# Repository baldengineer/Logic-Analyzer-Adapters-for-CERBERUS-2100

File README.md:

# CERBERUS 2100 Logic Analyzer Adapters

These adapters allow you to connect a logic analyzer to the CERBERUS 2100 expansion port--while having an expansion board connected.

For more information on the computer, check out the [CERBERUS 2100 project page](https://www.thebyteattic.com/p/cerberus-2100.html).

## One-To-One Adapter 
This adapter replicates the CERBERUS 2100's expansion port three times. Pins are mapped "1 to 1" across all three.

## Digital Digital Discovery Adapter
This adapter connects directly to a Digilent Digital Discovery and an expansion board. The signals on the left are grouped to match the input of the Digital Discovery.

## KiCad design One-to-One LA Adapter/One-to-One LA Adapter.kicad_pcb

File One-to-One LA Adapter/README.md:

## One-To-One Adapter

The One-to-one has three connectors. The middle connector plugs into the CERBERUS 2100's socket. The left header is intended for a logic analyzer. The right header is intended for an expansion board.

However, all three headers are connected in parallel.

### Status
Rev1 sent to fab. Still need to make Waveforms template and test the boards.

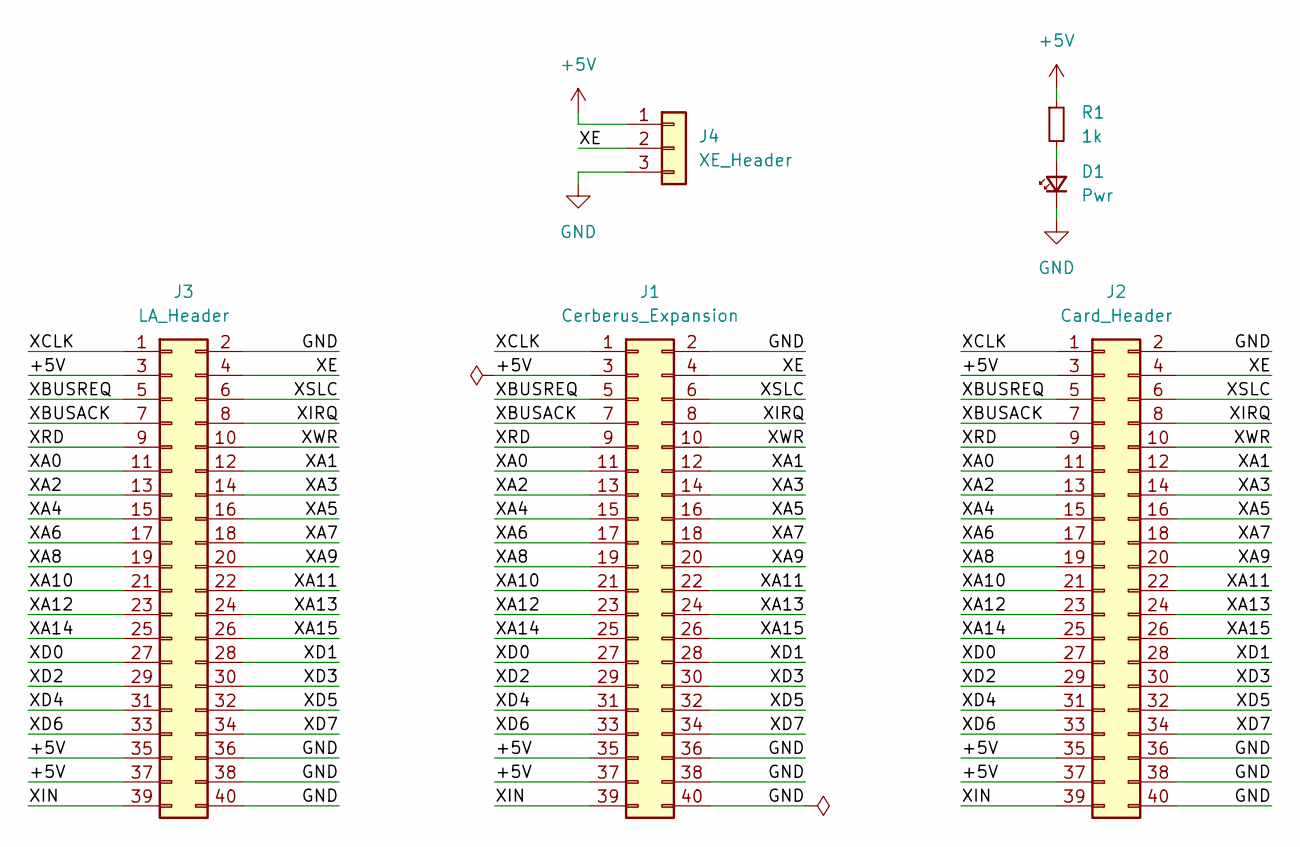
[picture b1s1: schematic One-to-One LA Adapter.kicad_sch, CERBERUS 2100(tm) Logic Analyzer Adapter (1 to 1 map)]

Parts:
D1: Pwr; LED_1206_3216Metric_Pad1.42x1.75mm_HandSolder
J1: Cerberus_Expansion; PinSocket_2x20_P2.54mm_Vertical
J2: Card_Header; PinHeader_2x20_P2.54mm_Vertical
J3: LA_Header; PinHeader_2x20_P2.54mm_Vertical
J4: XE_Header; PinHeader_1x03_P2.54mm_Vertical
R1: 1k; R_0805_2012Metric_Pad1.20x1.40mm_HandSolder

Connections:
+5V: J1.3, J1.35, J1.37, J2.3, J2.35, J2.37, J3.3, J3.35, J3.37, J4.1, R1.1
/XA0: J1.11, J2.11, J3.11
/XA1: J1.12, J2.12, J3.12
/XA2: J1.13, J2.13, J3.13
/XA3: J1.14, J2.14, J3.14
/XA4: J1.15, J2.15, J3.15
/XA5: J1.16, J2.16, J3.16
/XA6: J1.17, J2.17, J3.17
/XA7: J1.18, J2.18, J3.18
/XA8: J1.19, J2.19, J3.19
/XA9: J1.20, J2.20, J3.20
/XA10: J1.21, J2.21, J3.21
/XA11: J1.22, J2.22, J3.22
/XA12: J1.23, J2.23, J3.23
/XA13: J1.24, J2.24, J3.24
/XA14: J1.25, J2.25, J3.25
/XA15: J1.26, J2.26, J3.26
/XBUSACK: J1.7, J2.7, J3.7
/XBUSREQ: J1.5, J2.5, J3.5
/XCLK: J1.1, J2.1, J3.1
/XD0: J1.27, J2.27, J3.27
/XD1: J1.28, J2.28, J3.28
/XD2: J1.29, J2.29, J3.29
/XD3: J1.30, J2.30, J3.30
/XD4: J1.31, J2.31, J3.31
/XD5: J1.32, J2.32, J3.32
/XD6: J1.33, J2.33, J3.33
/XD7: J1.34, J2.34, J3.34
/XE: J1.4, J2.4, J3.4, J4.2
/XIN: J1.39, J2.39, J3.39
/XIRQ: J1.8, J2.8, J3.8
/XRD: J1.9, J2.9, J3.9
/XSLC: J1.6, J2.6, J3.6
/XWR: J1.10, J2.10, J3.10
GND: D1.1 (K), J1.2, J1.36, J1.38, J1.40, J2.2, J2.36, J2.38, J2.40, J3.2, J3.36, J3.38, J3.40, J4.3
unnamed: D1.2 (A), R1.2

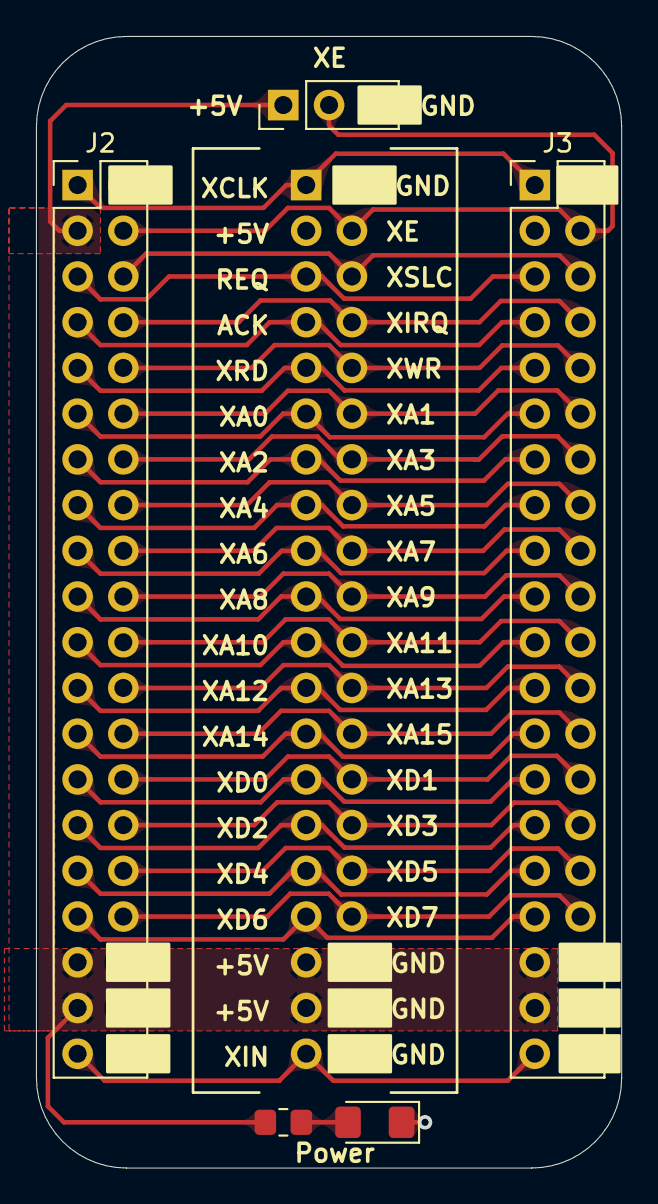
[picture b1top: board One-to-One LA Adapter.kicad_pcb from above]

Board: 2 copper layers, 32.5 x 62.9 mm, 6 parts (1 on the bottom side), 36 nets.

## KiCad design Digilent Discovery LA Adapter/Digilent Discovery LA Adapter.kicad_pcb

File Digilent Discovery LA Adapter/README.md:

## Digilent Discovery LA Adapter

This adapter is inteded to be used with a [Digilent Digital Discovery](https://digilent.com/shop/digital-discovery-portable-usb-logic-analyzer-and-digital-pattern-generator/). (Not the Analog Discovery!) These are USB-based logic analyzers that sample up to 100 MHz and 32 signals.

The center connector plugs into the socket. The right connector is for an expansion card. The left connector is for the Digital Discovery. 

Three connection options:
1. Use a short ribbon cable.
2. Mount the header upside-down.
3. Mount the header top-side-up.

### Waveforms Project File
Use the latest [beta version of Waveforms](https://forum.digilent.com/topic/8908-waveforms-beta-download/).

There is a bug with the pattern trigger. Addresses are reversed. So, to trigger on `0x0205` (`0000 0010 0000 0101`) you need to set the pattern to `0xA040` (`1010 0000 0100 0000`).

The clocks and control signals connect to the 24-32 inputs.

**CERBERUS 2100 Digital Discovery Template.dwf3work** is a starting project. It has all of the signals mapped for you! 

### Build Notes
Easily connect a Digilent Digital Discovery to a CERBERUS 2100. At a minimum, you'll need a 40-pin socket and a right-angle 32-pin socket. To act as an interposer between the CERBERUS and expansion card, you need a 40-pin header. There's also a spot for a 0805 resistor and 1206 LED for bling.

### OSH Park Link
The KiCad design files and PCB gerbers are available. Or you can order these boards directly from [OSH Park using this link](https://oshpark.com/shared_projects/0LsKYepP).

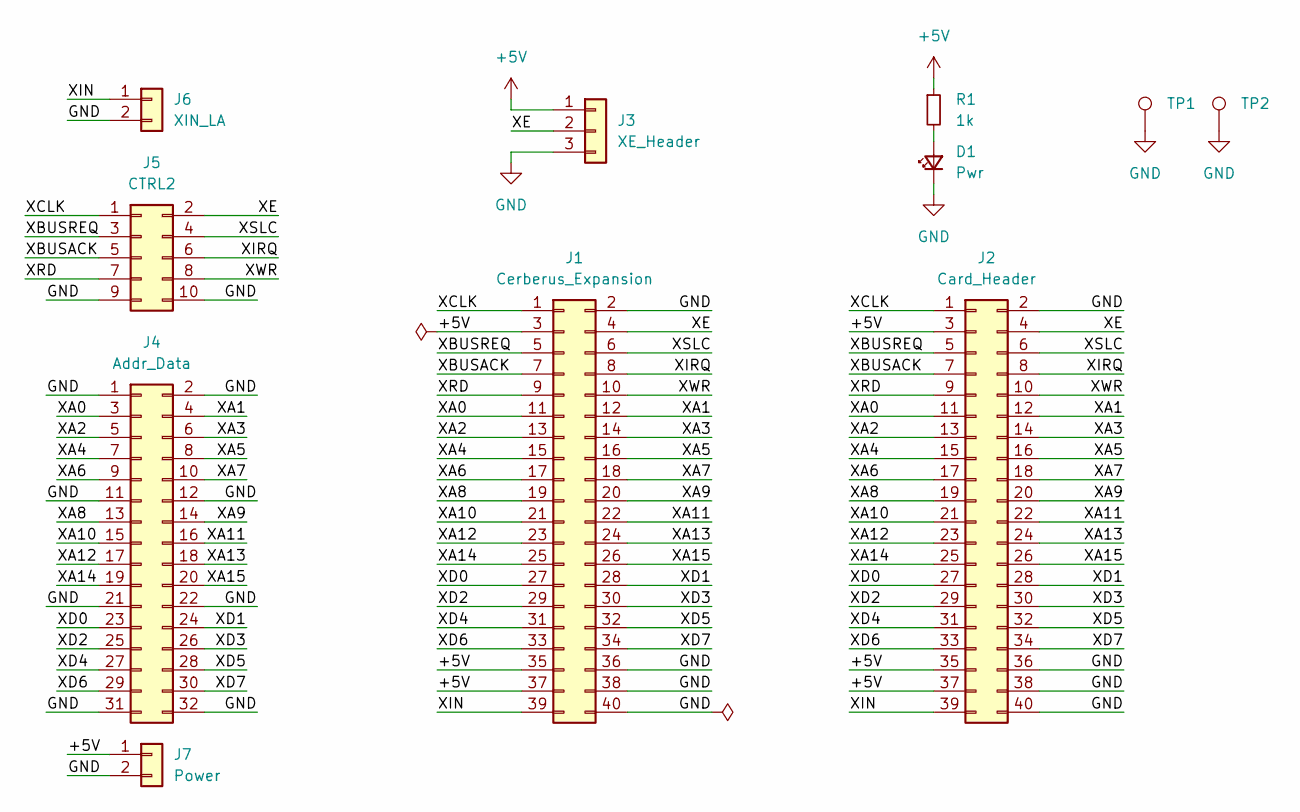
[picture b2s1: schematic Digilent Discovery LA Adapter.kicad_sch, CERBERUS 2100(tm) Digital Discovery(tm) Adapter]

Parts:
D1: Pwr; LED_1206_3216Metric_Pad1.42x1.75mm_HandSolder
J1: Cerberus_Expansion; PinSocket_2x20_P2.54mm_Vertical
J2: Card_Header; PinHeader_2x20_P2.54mm_Vertical
J3: XE_Header; PinHeader_1x03_P2.54mm_Vertical
J4: Addr_Data; PinSocket_2x16_P2.54mm_Vertical
J5: CTRL2; PinSocket_2x05_P2.54mm_Vertical
J6: XIN_LA; PinHeader_1x02_P2.54mm_Vertical
J7: Power; PinHeader_1x02_P2.54mm_Vertical
R1: 1k; R_0805_2012Metric_Pad1.20x1.40mm_HandSolder
TP1, TP2: TestPoint_Harwin; Harwin-S1751-46-Test-Point

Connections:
+5V: J1.3, J1.35, J1.37, J2.3, J2.35, J2.37, J3.1, J7.1, R1.1
/XA0: J1.11, J2.11, J4.3
/XA1: J1.12, J2.12, J4.4
/XA2: J1.13, J2.13, J4.5
/XA3: J1.14, J2.14, J4.6
/XA4: J1.15, J2.15, J4.7
/XA5: J1.16, J2.16, J4.8
/XA6: J1.17, J2.17, J4.9
/XA7: J1.18, J2.18, J4.10
/XA8: J1.19, J2.19, J4.13
/XA9: J1.20, J2.20, J4.14
/XA10: J1.21, J2.21, J4.15
/XA11: J1.22, J2.22, J4.16
/XA12: J1.23, J2.23, J4.17
/XA13: J1.24, J2.24, J4.18
/XA14: J1.25, J2.25, J4.19
/XA15: J1.26, J2.26, J4.20
/XBUSACK: J1.7, J2.7, J5.5
/XBUSREQ: J1.5, J2.5, J5.3
/XCLK: J1.1, J2.1, J5.1
/XD0: J1.27, J2.27, J4.23
/XD1: J1.28, J2.28, J4.24
/XD2: J1.29, J2.29, J4.25
/XD3: J1.30, J2.30, J4.26
/XD4: J1.31, J2.31, J4.27
/XD5: J1.32, J2.32, J4.28
/XD6: J1.33, J2.33, J4.29
/XD7: J1.34, J2.34, J4.30
/XE: J1.4, J2.4, J3.2, J5.2
/XIN: J1.39, J2.39, J6.1
/XIRQ: J1.8, J2.8, J5.6
/XRD: J1.9, J2.9, J5.7
/XSLC: J1.6, J2.6, J5.4
/XWR: J1.10, J2.10, J5.8
GND: D1.1 (K), J1.2, J1.36, J1.38, J1.40, J2.2, J2.36, J2.38, J2.40, J3.3, J4.1, J4.2, J4.11, J4.12, J4.21, J4.22, J4.31, J4.32, J5.9, J5.10, J6.2, J7.2, TP1.1, TP2.1
unnamed: D1.2 (A), R1.2

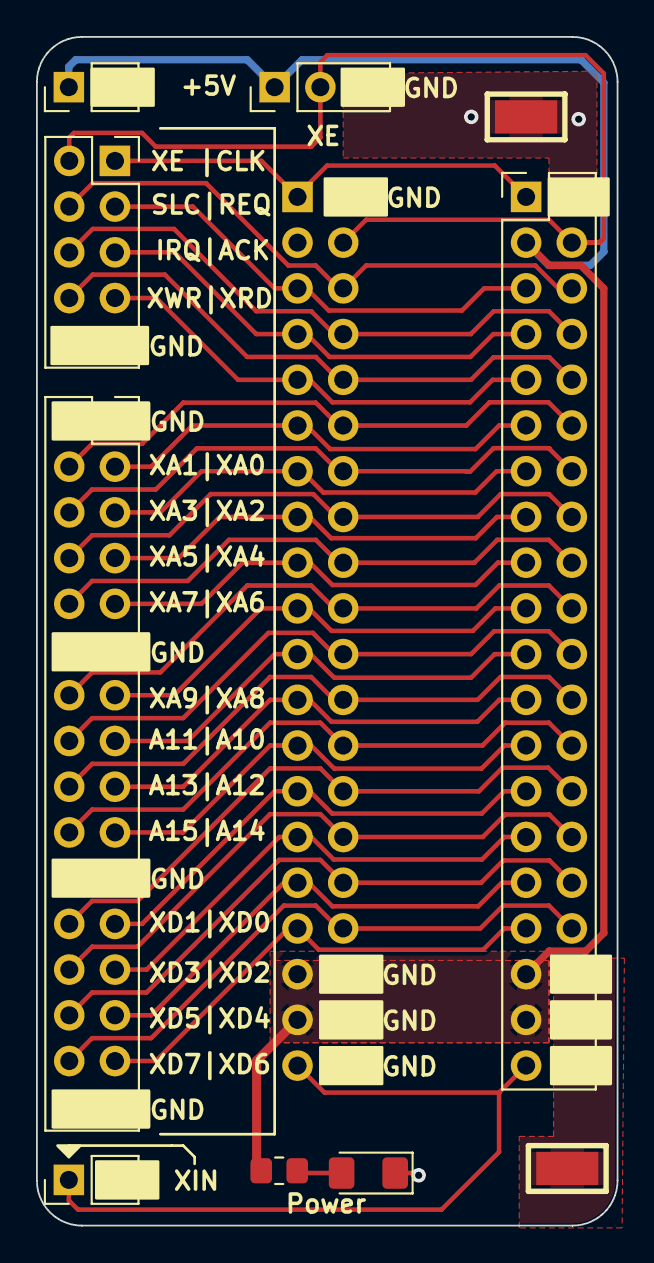
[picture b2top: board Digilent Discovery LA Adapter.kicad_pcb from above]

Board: 2 copper layers, 32.3 x 66.0 mm, 11 parts (1 on the bottom side), 36 nets.

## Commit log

2024-04-11 ignore the things
2024-04-11 initial commit (for the 1-to-1 adapter)
2024-04-11 initial expansion connector layout
2024-04-11 one-to-one ready for pcb
2024-04-12 unrouted 0
2024-04-12 added teardrops
2024-04-12 one-to-one rev1 ready for fab
2024-04-12 Added License (CC-SA) and Readme.
2024-04-12 readme fix
2024-04-12 more readme fixes
2024-04-12 read.me updates
2024-04-12 readme: racking up the commits!
2024-04-12 Create README.md for 1:1
2024-04-12 initial commit for digital discovery adapter
2024-04-12 Copied Sch headers from Mega IIe
2024-04-12 cleared net labels
2024-04-12 labeled DD headers in sch and updated to pcb
2024-04-12 thermal drc "error"
2024-04-12 about to delete extra silk
2024-04-12 dd adapter rev 1 ready to go to the fab
2024-04-12 Documentation updates. (No design changes made.)
2024-04-26 added an image for DD adapter
2024-04-26 Wavewforms Project and instructions
2024-04-26 readme fixes
